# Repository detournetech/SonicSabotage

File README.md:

Sonic Sabotage

- Bluetooth LE 4.2 based buzzer
- "Just Works" pairing mode, or "Numeric Comparison" for additional security features
- Set beeps on peroidic or random schedule
- Luminosity and RSSI based thresholds also available
- Over-the-air firmware updates
- Support for Android and Linux clients, iOS support coming soon

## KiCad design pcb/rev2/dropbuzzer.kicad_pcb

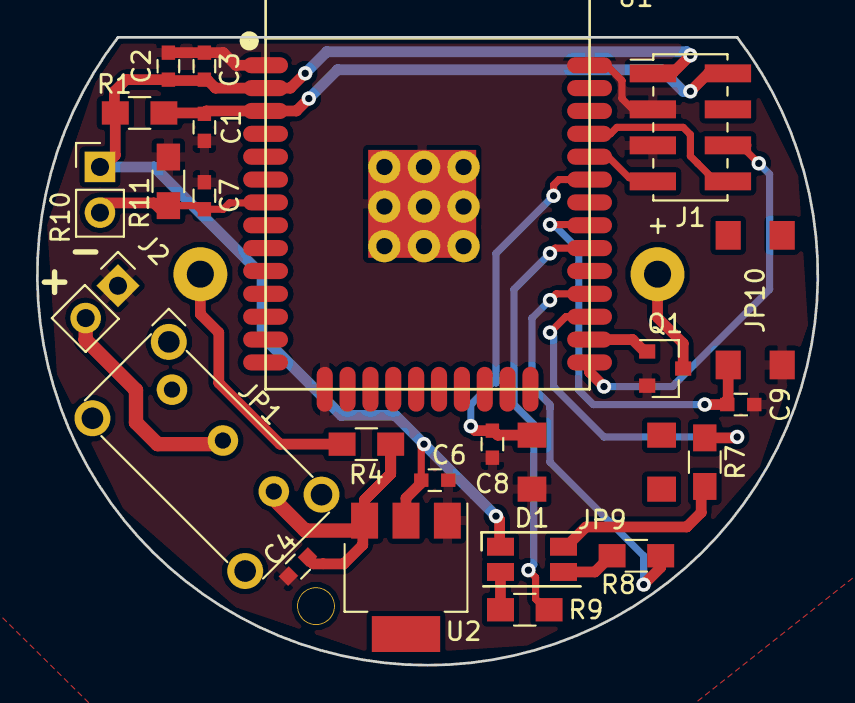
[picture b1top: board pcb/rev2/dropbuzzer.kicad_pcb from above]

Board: 2 copper layers, 43.4 x 34.9 mm, 25 parts (1 on the bottom side), 20 nets.

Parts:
BZ1: Buzzer; bigbuzz
C1, C7: 1nF; C_0603
C2: 100uF; C_0603
C3: 1uF; C_0603
C4: 10uF; C_0603
C6: 22uF; C_0603
C8, C9: 1nF/50V; C_0603
D1: LED_ARGB; LED_RGB_1210
J1: Conn_02x04_Counter_Clockwise; Pin_Header_Straight_2x04_Pitch2.00mm_SMD
J2: PWR_IN; Pin_Header_Straight_1x02_Pitch2.54mm
JP1: Jumper_NC_Dual; EG1224
JP9, JP10: Button; tl3305
Q1: 2N2219; SOT-23
R1: 12K; R_0805_HandSoldering
R4: 1k; R_0805_HandSoldering
R7, R8, R9: 330; R_0805_HandSoldering
R10: R_PHOTO; Pin_Header_Straight_1x02_Pitch2.54mm
R11: 10k; R_0805_HandSoldering
U1: ESP32-WROOM
U2: NCP1117DT12G; SOT-223

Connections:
+BATT: C4.1, JP1.3, R4.1, U2.3
/B: R9.1, U1.30
/BOOT: J1.6, U1.25
/EN: C1.1, J1.2, R1.2, U1.3
/G: R8.1, U1.28
/OTA: C9.1, JP10.3, U1.31
/PHOTO: C7.1, R10.2, R11.1, U1.7
/R: R7.1, U1.27
/RX: J1.7, U1.34
/SEC: C8.1, JP9.3, U1.33
/T: Q1.1, U1.26
/TX: J1.8, U1.35
GND: C1.2, C2.2, C3.2, C4.2, C6.2, C7.2, C8.2, C9.2, J1.3, J1.5, J2.1, JP9.1, JP10.1, Q1.2, R11.2, U1.1, U1.15, U1.38, U1.39, U2.1
unnamed: BZ1.1, R4.2
unnamed: BZ1.2, Q1.3
unnamed: D1.2, R9.2
unnamed: D1.3, R8.2
unnamed: D1.4, R7.2
unnamed: J2.2, JP1.2
VDD: C2.1, C3.1, C6.1, D1.1, J1.1, R1.1, R10.1, U1.2, U2.2

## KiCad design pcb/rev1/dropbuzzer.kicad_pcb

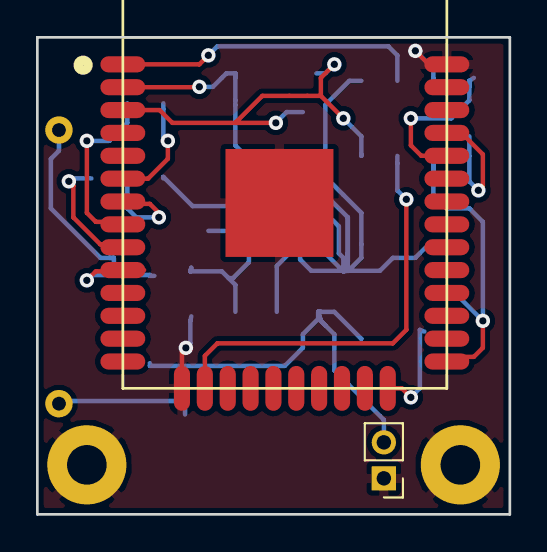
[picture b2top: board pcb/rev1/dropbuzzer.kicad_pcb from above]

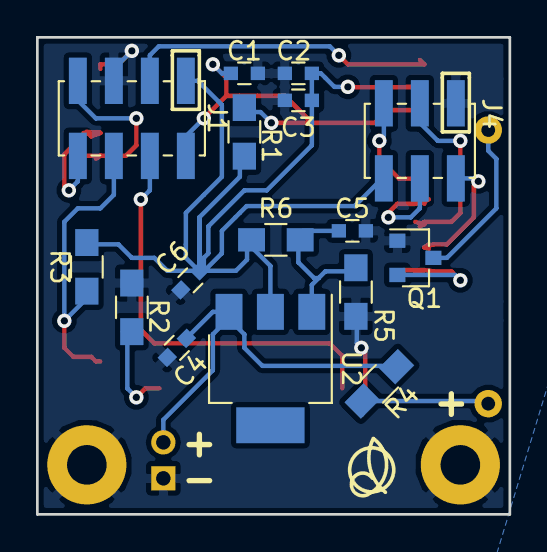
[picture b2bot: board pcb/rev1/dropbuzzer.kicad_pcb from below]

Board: 2 copper layers, 26.2 x 26.5 mm, 16 parts (16 on the bottom side), 6 nets.

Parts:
C1: 1nF; C_0603
C2: 100uF; C_0603
C3: 1uF; C_0603
C4, C5: 10uF; C_0603
C6: 22uF; C_0603
J1: Conn_02x04_Counter_Clockwise; Pin_Header_Straight_2x04_Pitch2.00mm_SMD
J4: CONN_01X06; Pin_Header_Straight_2x03_Pitch2.00mm_SMD
Q1: 2N2219; SOT-23
R1: 12K; R_0805_HandSoldering
R2, R3: 5K; R_0805_HandSoldering
R4: 1k; R_0805_HandSoldering
R5: 0R; R_0805_HandSoldering
R6: 3.3k; R_0805_HandSoldering
U2: NCP1117DT12G; SOT-223

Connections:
+9V: C4.1, R4.1, U2.3
/EN: C1.1, J1.2, R1.2
/P6: J1.6, R3.2
GND: C1.2, C2.2, C3.2, C4.2, C5.2, C6.2, J1.5, J4.1, Q1.1, R2.2, R5.2
unnamed: C5.1, R5.1, R6.2, U2.1
VDD: C2.1, C3.1, C6.1, J1.1, J4.6, R1.1, R3.1, R6.1, U2.2

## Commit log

2018-08-18 add picture
2018-08-22 rm local git config
2018-08-22 more descriptive icons
2018-08-22 add state diagram for documentation
2018-08-22 explicitly set mode characteristic before doing something
2018-08-23 rm OTA bug, add beep indication, config for less space
2018-08-29 wait until password arrives to connect to AP
2018-08-29 gitignore
2018-08-29 fix hardcoded strings
2018-08-29 add french locale
